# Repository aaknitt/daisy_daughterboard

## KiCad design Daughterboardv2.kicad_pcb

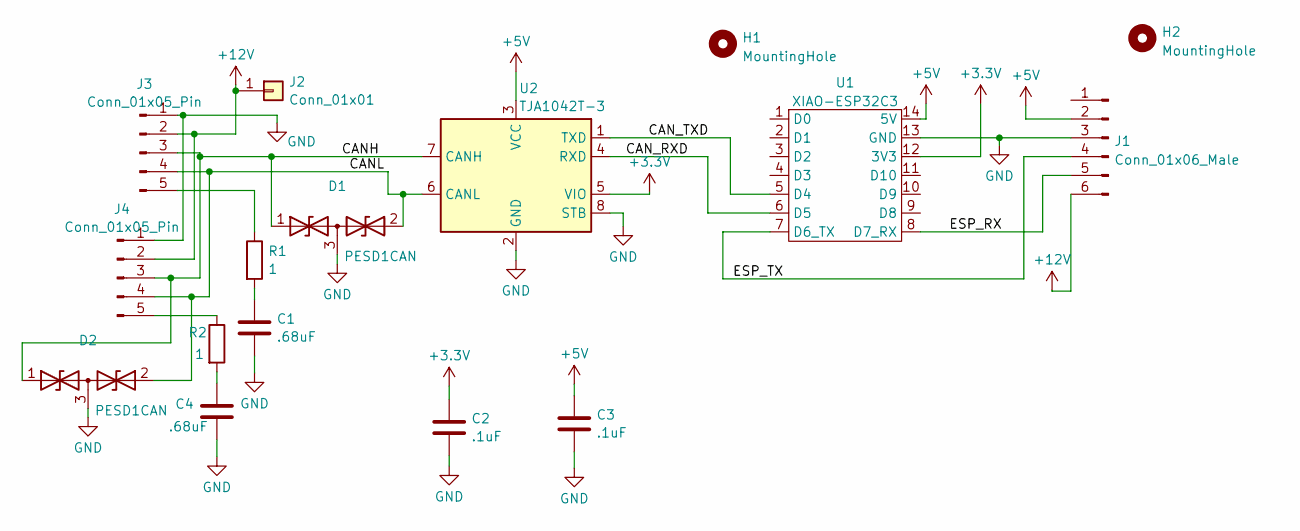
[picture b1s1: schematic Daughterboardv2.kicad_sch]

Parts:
C1, C4: .68uF; C_0805_2012Metric_Pad1.18x1.45mm_HandSolder
C2, C3: .1uF; C_0805_2012Metric_Pad1.18x1.45mm_HandSolder
D1, D2: PESD1CAN; SOT-23
H1, H2: MountingHole; MountingHole_2.7mm_M2.5_DIN965
J1: Conn_01x06_Male; PinHeader_1x06_P2.54mm_Vertical
J2: Conn_01x01; TestPoint_THTPad_2.0x2.0mm_Drill1.0mm
J3: Conn_01x05_Pin; TerminalBlock_4Ucon_1x05_P3.50mm_Horizontal
J4: Conn_01x05_Pin; JST_PH_S5B-PH-SM4-TB_1x05-1MP_P2.00mm_Horizontal
R1, R2: 1; R_0805_2012Metric_Pad1.20x1.40mm_HandSolder
U1: XIAO-ESP32C3; XIAO-ESP32C3_smt
U2: TJA1042T-3; SOIC-8_3.9x4.9mm_P1.27mm

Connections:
+3.3V: C2.1, U1.12 (3V3), U2.5 (VIO)
+5V: C3.1, J1.2, U1.14 (5V), U2.3 (VCC)
+12V: J1.6, J2.1, J3.2, J4.2
/CANH: D1.1 (A1), D2.1 (A1), J3.3, J4.3, U2.7 (CANH)
/CANL: D1.2 (A2), D2.2 (A2), J3.4, J4.4, U2.6 (CANL)
/CAN_RXD: U1.6 (D5), U2.4 (RXD)
/CAN_TXD: U1.5 (D4), U2.1 (TXD)
/ESP_RX: J1.5, U1.8 (D7_RX)
/ESP_TX: J1.4, U1.7 (D6_TX)
GND: C1.2, C2.2, C3.2, C4.2, D1.3 (common), D2.3 (common), J1.3, J3.1, J4.1, U1.13 (GND), U2.2 (GND), U2.8 (STB)
unnamed: C1.1, R1.2
unnamed: C4.1, R2.2
unnamed: J3.5, R1.1
unnamed: J4.5, R2.1

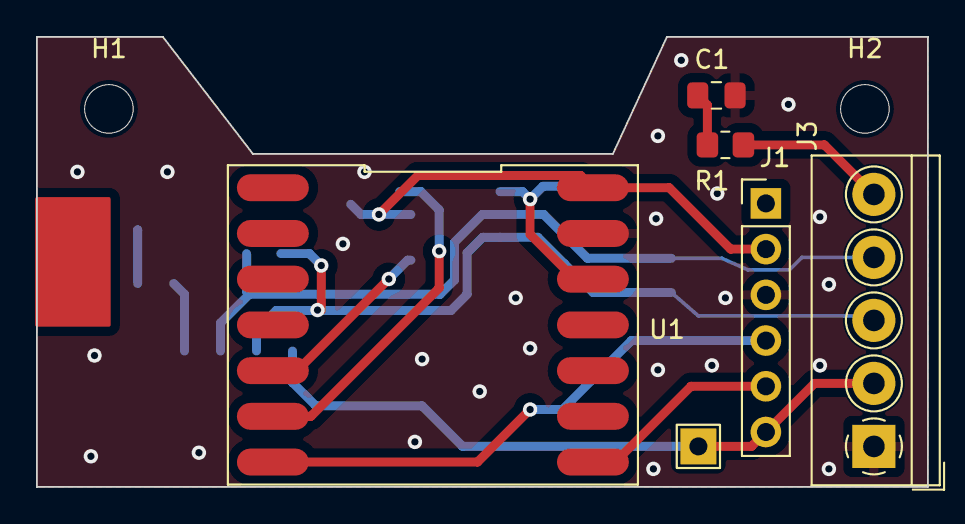
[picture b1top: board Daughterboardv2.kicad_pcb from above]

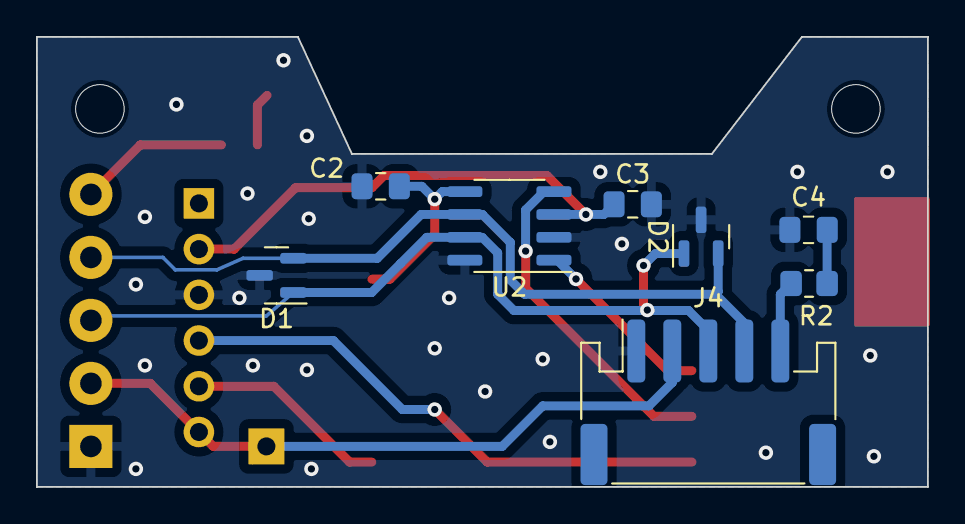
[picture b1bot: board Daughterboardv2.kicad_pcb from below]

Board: 2 copper layers, 49.5 x 25.0 mm, 16 parts (8 on the bottom side), 14 nets.

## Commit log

2024-03-18 add second option for CAN transorb
2024-04-04 schematic and pcb bug fix for Vcc and Vio swap on CAN xcvr
